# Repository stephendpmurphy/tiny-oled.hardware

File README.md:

# ATtiny OLED

## Description
This project is intended to challenge myself and be used as a way to explore and try new concepts in electrical hardware design. The current planned challenges are as follows
- Design and maintain a full PCB in KiCad
- Use 0402 components as much as possible (my current standard is 0603)
- Create a board that is easily testable and probe friendly (test pads galore)
- Add a 128x64 OLED driver and connector
- Add a coin-cell battery holder
- Add side-fire push-buttons for the UI
- Add I2c addressable RGB LEDs
- Add a SD card using a SPI interface to the host MCU
- Focus on low power consumption to preserve battery life
- Add FTDI bridge to give USB connectivity to the host MCU over UART

## Hardware
For this project I will be using an [ATtiny87 from Atmel/Microchip](https://www.microchip.com/wwwproducts/en/ATTINY87). The part has a limited feature set and a small amount of memory, but hopefully enough to implement everything desired and provide an adequate challenge. 
- 8KB of Flash
- 512B or SRAM
- 512B of EEPROM
- 1x UART
- 2x SPI
- 1x I2c

The project for the firmware can be found in the [tiny-oled.firmware](https://github.com/stephendpmurphy/tiny-oled.firmware) repository on my profile. The project will be created and managed using the open source electrical design suite, [KiCad](https://kicad-pcb.org/).

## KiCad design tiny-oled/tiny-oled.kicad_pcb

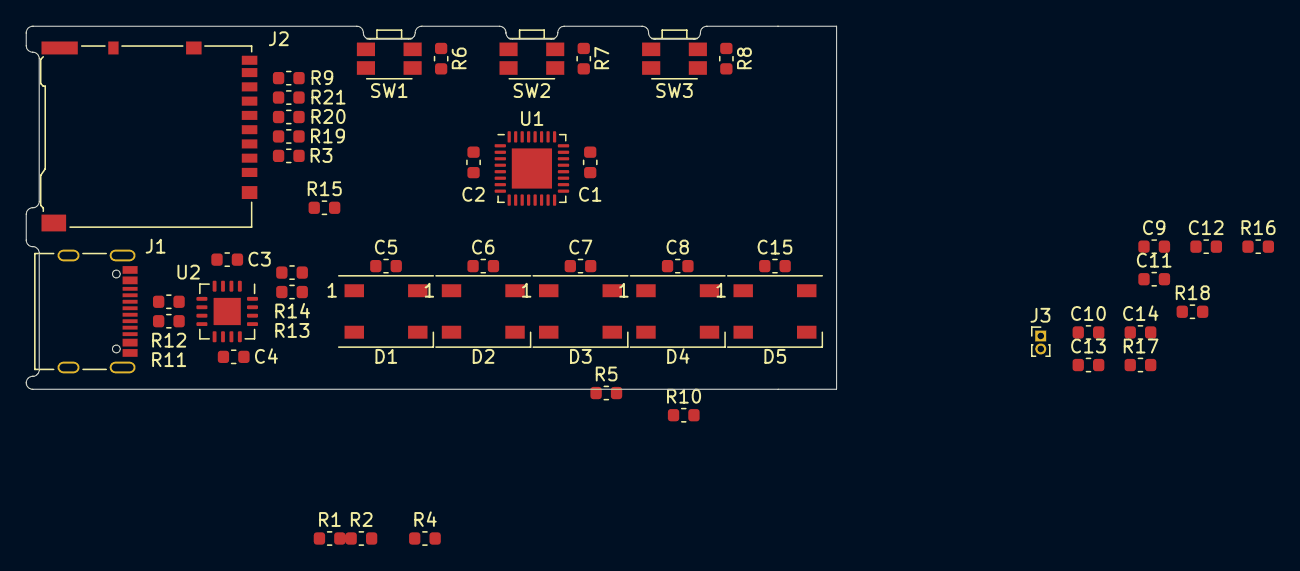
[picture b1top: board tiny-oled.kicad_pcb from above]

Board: 2 copper layers, 62.5 x 28.0 mm, 49 parts (0 on the bottom side), 35 nets, no tracks yet.

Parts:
C1, C2, C3, C4, C5, C6, C7, C8, C15: .1uF; C_0603_1608Metric
C9, C10, C12, C14: 1uF; C_0603_1608Metric
C11, C13: 10uF; C_0603_1608Metric
D1, D2, D3, D4, D5: WS2812B; LED_WS2812B_PLCC4_5.0x5.0mm_P3.2mm
J1: USB4085-GF-A; USB_C_Receptacle_Palconn_UTC16-G
J2: Micro_SD_Card_Det_Hirose_DM3AT; microSD_HC_Hirose_DM3AT-SF-PEJM5
J3: F32Q-1A7H1-11015; PinHeader_1x02_P1.00mm_Vertical
R1, R2, R3, R4, R5, R6, R7, R8, R9, R10: 10k; R_0603_1608Metric
R11, R12: 27; R_0603_1608Metric
R13, R14, R17, R18, R19, R20, R21: 0; R_0603_1608Metric
R15: 470; R_0603_1608Metric
R16: 560k; R_0603_1608Metric
SW1, SW2, SW3: EVQP7A; SW_SPST_EVQP7A
U1: ATtiny87-MU; QFN-32-1EP_5x5mm_P0.5mm_EP3.1x3.1mm
U2: FT230XQ; QFN-16-1EP_4x4mm_P0.65mm_EP2.1x2.1mm

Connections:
GND: C1.2, C2.2, C3.2, C4.2, C5.2, C6.2, C7.2, C8.2, C9.2, C10.2, C11.2, C13.2, C15.2, D1.3, D2.3, D3.3, D4.3, D5.3, J1.A1, J1.A12, J1.B1, J1.B12, J1.S1, J2.6, J2.9, J2.11, R16.2, SW1.2, SW2.2, SW3.2, U1.5, U1.21, U1.33, U2.3, U2.13, U2.17
unnamed: C14.1, J3.1
unnamed: C14.2, J3.2
unnamed: D1.2, D2.4
unnamed: D1.4, R15.1
unnamed: D2.2, D3.4
unnamed: D3.2, D4.4
unnamed: D4.2, D5.4
unnamed: J1.A6, J1.B6, R12.2
unnamed: J1.A7, J1.B7, R11.2
unnamed: J2.3, R19.1
unnamed: J2.5, R20.1
unnamed: J2.7, R21.1
unnamed: R13.2, U2.15
unnamed: R14.1, U2.2
SPI_MISO: R21.2, U1.31
SPI_MOSI: R18.2, R19.2, U1.9
SPI_SCK: R17.2, R20.2, U1.10
SSD1306_DC: R5.2, U1.12
UART_RX: R13.1, U1.30
UART_TX: R14.2, U1.29
USB_DM: R11.1, U2.7
USB_DP: R12.1, U2.6
USB_VBUS: J1.A4, J1.A9, J1.B4, J1.B9
VCC: C1.1, C2.1, C3.1, C4.1, C5.1, C6.1, C7.1, C8.1, C9.1, C10.1, C15.1, D1.1, D2.1, D3.1, D4.1, D5.1, J2.4, R1.1, R2.1, R3.1, R4.1, R5.1, R6.1, R7.1, R8.1, R9.1, R10.1, U1.4, U1.20, U2.1, U2.10
WS2812_DO: R15.2, U1.15
~BTN1: R6.2, SW1.1, U1.28
~BTN2: R7.2, SW2.1, U1.27
~BTN3: R8.2, SW3.1, U1.26
~RESET: R10.2, U1.14, U2.9
~SD_DETECT: J2.10, R9.2, U1.25
~SPI_CS_BME280: R2.2, U1.18
~SPI_CS_SD: J2.2, R3.2, U1.3
~SPI_CS_SSD1306: R1.2, U1.19
~SSD1306_RESET: R4.2, U1.11

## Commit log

2020-07-30 Adding a License and filling out the Readme
2020-08-17 Adding first pass at the schematic and PCB layout
